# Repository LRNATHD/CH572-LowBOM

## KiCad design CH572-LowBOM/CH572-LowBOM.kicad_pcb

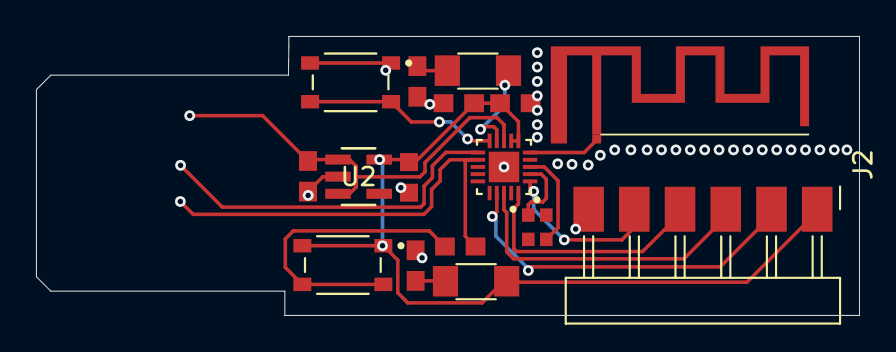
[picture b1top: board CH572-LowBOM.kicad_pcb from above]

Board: 2 copper layers, 45.7 x 15.5 mm, 17 parts (1 on the bottom side), 17 nets.

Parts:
C1, C2: C_0603; 0603
C6: 2.2uF; 0603
C7: 0.1uF; 0603
D1, D2: PWRLED; LED_1206
E2: 2.4ghz; antenna
J1: USB_A_PCB_Edge_receptacle
J2: PinHeader_01x06_P2.54mm_Horizontal_SMD
R3: 1.5k; 0603
R4, R5: 330; 0603
S1, S2: TL3365AF180QG; button
U1: CH572D
U2: TCR2EF33_LMCT; voltage regulator
Y1: XRCGB32M000F2P01R0; 32mhz crystal

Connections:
D+: J1.3 (D+), R3.2, U1.12 (PA1/UDP/R3/T2/SDA1)
D-: J1.2 (D-), U1.11 (PA0/UDM/R2/T3/SCL1)
unnamed: D1.1 (K), R5.2
unnamed: D2.1 (K), R4.2
unnamed: R3.1, S1.3, S1.4
unnamed: E2.1, U1.5 (ANT)
unnamed: U1.3 (XI), Y1.3
unnamed: U1.2 (XO), Y1.1
PA2: J2.4, U1.20 (PA2/R/T1/SDA2/SCS_/PWM2/TMR1/CN)
PA3: J2.5, U1.1 (PA3/T/R1/SCL2/SCK_/PWM3/CP0)
PA9: D2.2 (A), U1.9 (PA9/SDA/R5/TMR3)
PA10: J2.2, U1.17 (PA10/R6/T7)
PA11: J2.3, U1.18 (PA11/R7/T6)
PWR_3V3: C1.1, C6.1, C7.1, D1.2 (A), J2.1, S1.1, S1.2, U1.6 (VDD33), U1.7 (VIO33), U2.5 (VOUT)
PWR_5V: C2.1, J1.1 (VBUS), U1.8 (V5), U2.1 (VIN), U2.3 (CONTROL)
PWR_GND: C1.2, C2.2, C6.2, C7.2, J1.4 (GND), J2.6, R4.1, R5.1, S2.1, S2.2, U1.21 (GND/EPAD), U2.2 (GND)
RST: S2.3, S2.4, U1.10 (PA8/SCL/T5/PWM5/RST)

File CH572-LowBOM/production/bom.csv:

Designator,Footprint,Quantity,Value,LCSC Part #
"C1, C2",0603,2,C_0603,
C6,0603,1,2.2uF,
C7,0603,1,0.1uF,
"D1, D2",LED_1206,2,PWRLED,
E2,antenna,1,2.4ghz,
J1,USB_A_PCB_Edge_receptacle,1,USB_A_PCB_Edge_receptacle,
J2,PinHeader_01x06_P2.54mm_Horizontal_SMD,1,PinHeader_01x06_P2.54mm_Horizontal_SMD,
R3,0603,1,1.5k,
"R4, R5",0603,2,330,
"S1, S2",button,2,TL3365AF180QG,
U1,CH572D,1,~,
U2,voltage regulator,1,TCR2EF33_LMCT,
Y1,32mhz crystal,1,XRCGB32M000F2P01R0,

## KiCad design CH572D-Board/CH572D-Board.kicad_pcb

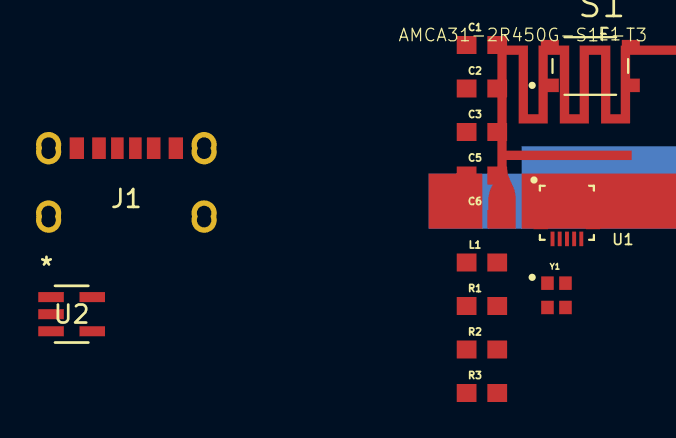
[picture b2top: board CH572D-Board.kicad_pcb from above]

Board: 2 copper layers, 15 parts (0 on the bottom side), 9 nets, no tracks yet.

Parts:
C1: 0.1uF; 0603
C2: 1uF; 0603
C3: 1.5pF; 0603
C5, C6: 2.2uF; 0603
E1: AMCA31-2R450G-S1F-T3; pcbantenna
J1: Conn_USB_C_Socket; Conn_USB_C_Socket_GCT_USB4125-GF-A-0190
L1: 3.9nH; 0603
R1, R2: 5.1k; 0603
R3: 1.5k; 0603
S1: TL3365AF180QG; button
U1: CH572D
U2: TCR2EF33_LMCT; voltage regulator
Y1: 32mhz; 32mhz crystal

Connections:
+3.3V: C2.2, C6.1, S1.1, S1.2, U1.6 (VDD33), U1.7 (VIO33)
ANTENNA: C3.2, L1.2
GND: C1.1, C2.1, C3.1, C5.2, C6.2, R1.1, R2.1, U1.21 (GND/EPAD)
unnamed: R3.1, S1.3, S1.4
unnamed: E1.1, U1.5 (ANT)
unnamed: C5.1, U1.8 (V5)
unnamed: U1.3 (XI), Y1.1
unnamed: U1.2 (XO), Y1.3
PA1: R3.2, U1.12 (PA1/UDP/R3/T2/SDA1)

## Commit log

2025-10-07 started work
    found a usb a module thats just based off pcb
2025-10-07 tryiung to get comits working
    help me!
2025-10-07 small works making sure everything going green
    none
2025-10-07 nearly just got it done
    looks kinda goofy, but real small and decent enough example
2025-10-08 work done kinda needs a bit more
2025-10-09 work
2025-10-09 done?
    plugs in like a usb,
2025-10-09 final of the night
2025-12-11 Add image to README for USB dongle project
